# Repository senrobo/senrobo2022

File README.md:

# Sentinels Robotics

Yay we passed the 100th commit milestone
400 Commit milestone

## Checklist

### Mechanical

- Kicker Done on 20/1/2022

### Parts used

| Part Name    | Part Description                                               |
| ------------ | -------------------------------------------------------------- |
| OpenMV H7/R7 | Camera                                                         |
| MUX          | Multiplexer (https://www.ti.com/lit/ds/symlink/cd74hc4067.pdf) |

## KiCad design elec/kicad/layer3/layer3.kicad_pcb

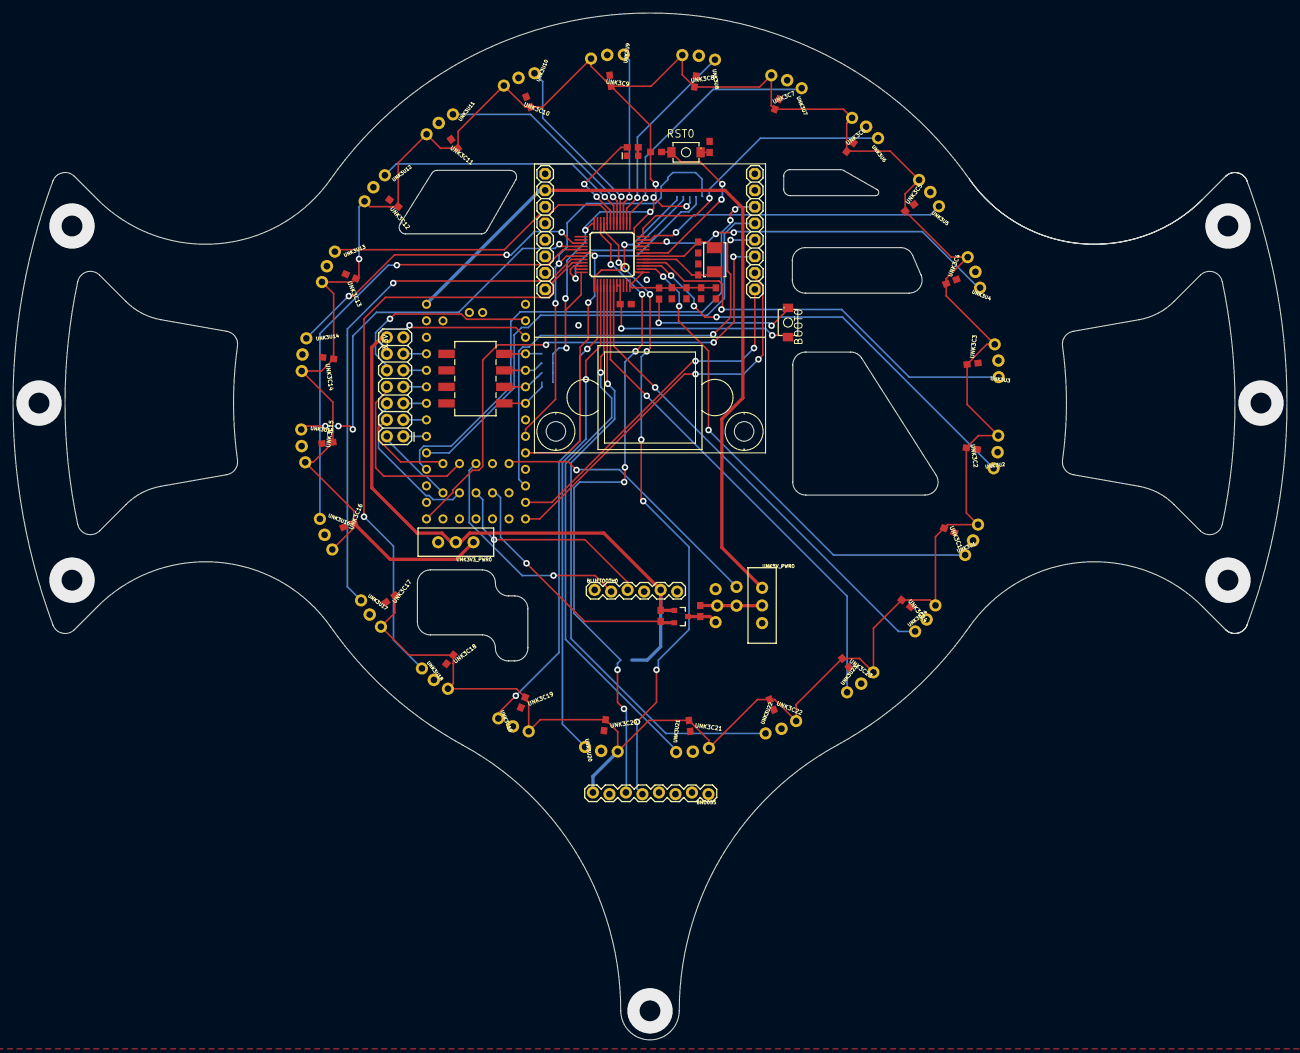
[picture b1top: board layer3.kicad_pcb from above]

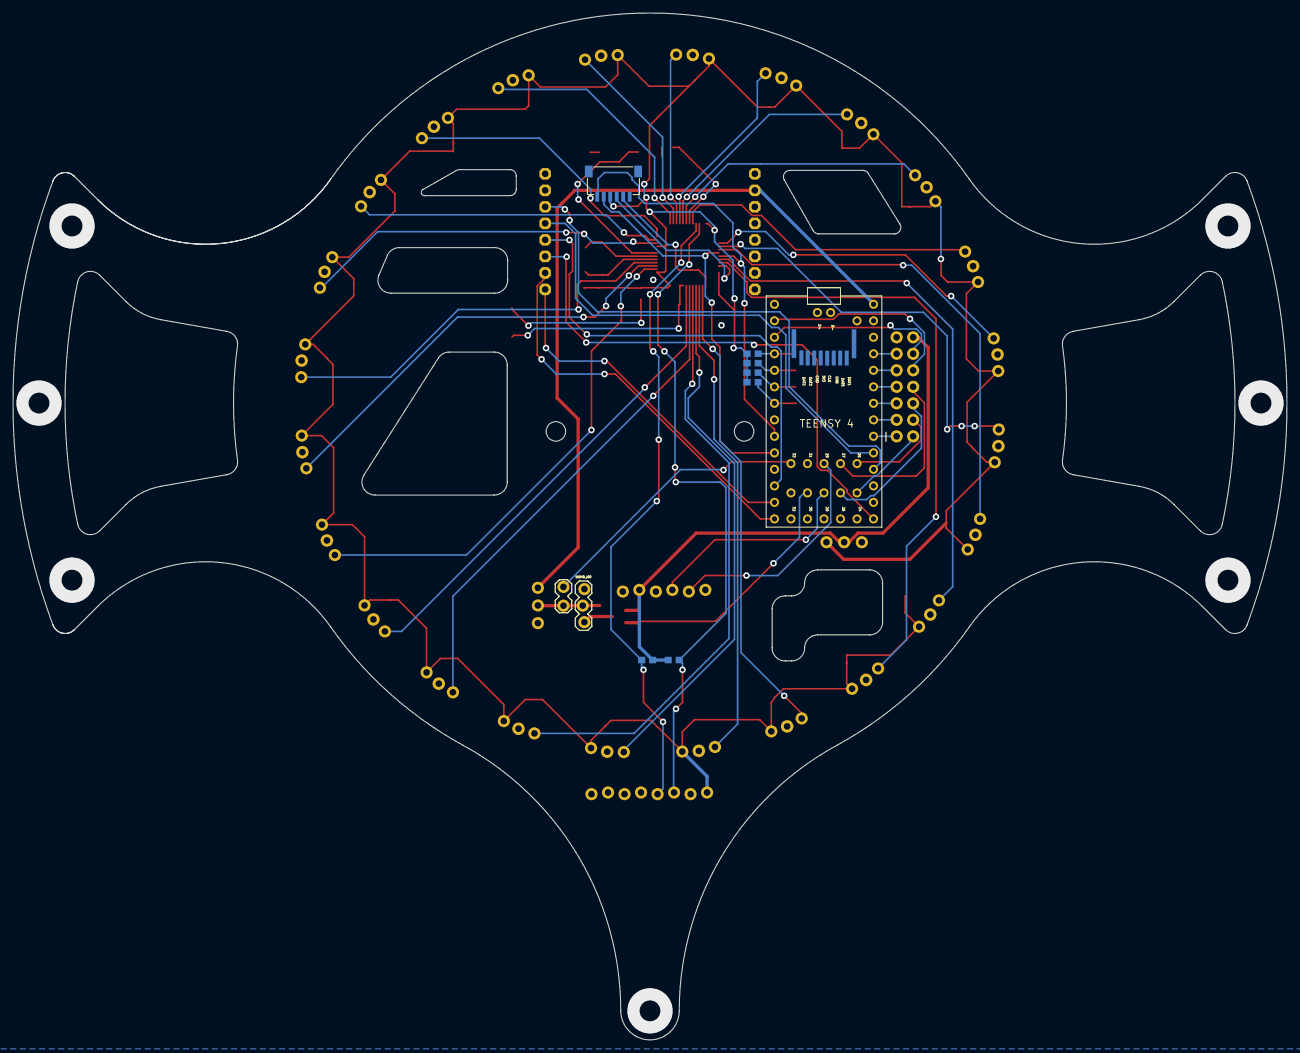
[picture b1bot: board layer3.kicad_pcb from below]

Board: 2 copper layers, 196.0 x 158.0 mm, 84 parts (10 on the bottom side), 70 nets.

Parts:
BLUETOOTH0: HC-05
BNO055: 1X08_LOCK
BOOT0: MOMENTARY_SWITCH_4X3
C1, C2, C3, C5: 1uF; C0603
C6, C7: 22pF; C0603
D1: BLUE; LED-0603
J1: 1X02_LOCK
Q2: AO3402; SOT23-3
R1, R4, R6, R7, R8, R9: 10k; R0603
R2, R3: 1k; R0603
R5: 470; R0603
R10, R11: 4.7k; 0603
R12, R13: 4.7k; R0603
RST0: MOMENTARY_SWITCH_4X3
S1: DIP-04SMD; DIPSWITCH-04-SMD
SERVO_IO0: 1X03_LOCK
STM32_IR0: STM32F103CBT6; LQFP48
TEENSY4: TEENSY-4.0-FULL-BREAKOUT-PINS
U$8: OPENMV3
U$14: CONN_07X2; 2X7
UNK3C1, UNK3C2, UNK3C3, UNK3C4, UNK3C5, UNK3C6, UNK3C7, UNK3C8, UNK3C9, UNK3C10, UNK3C11, UNK3C12, UNK3C13, UNK3C14, UNK3C15, UNK3C16, UNK3C17, UNK3C18, UNK3C19, UNK3C20, UNK3C21, UNK3C22, UNK3C23, UNK3C24: C0603
UNK3U1, UNK3U2, UNK3U3, UNK3U4, UNK3U5, UNK3U6, UNK3U7, UNK3U8, UNK3U9, UNK3U10, UNK3U11, UNK3U12, UNK3U13, UNK3U14, UNK3U15, UNK3U16, UNK3U17, UNK3U18, UNK3U19, UNK3U20, UNK3U21, UNK3U22, UNK3U23, UNK3U24: TSSP58038
UNK3V3_PWR0, UNK5V_PWR0: SWITCH_SPDT_PTH_11.6X4.0MM_LOCK
X1: SM06B-SRSS-TB
Y1: 8MHz; CRYSTAL-SMD-5X3.2-2PAD

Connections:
3.3V: BLUETOOTH0.5, Q2.1, R10.2, R11.2, R13.1, U$14.14, UNK3V3_PWR0.2
3V3_SWITCH: BNO055.8, C1.1, C2.1, C3.1, C5.2, R1.2, R3.2, R6.2, R7.2, R8.2, R9.2, STM32_IR0.1, STM32_IR0.9, STM32_IR0.24, STM32_IR0.36, STM32_IR0.48, UNK3C1.1, UNK3C2.1, UNK3C3.1, UNK3C4.1, UNK3C5.1, UNK3C6.1, UNK3C7.1, UNK3C8.1, UNK3C9.1, UNK3C10.1, UNK3C11.1, UNK3C12.1, UNK3C13.1, UNK3C14.1, UNK3C15.1, UNK3C16.1, UNK3C17.1, UNK3C18.1, UNK3C19.1, UNK3C20.1, UNK3C21.1, UNK3C22.1, UNK3C23.1, UNK3C24.1, UNK3U1.VS, UNK3U2.VS, UNK3U3.VS, UNK3U4.VS, UNK3U5.VS, UNK3U6.VS, UNK3U7.VS, UNK3U8.VS, UNK3U9.VS, UNK3U10.VS, UNK3U11.VS, UNK3U12.VS, UNK3U13.VS, UNK3U14.VS, UNK3U15.VS, UNK3U16.VS, UNK3U17.VS, UNK3U18.VS, UNK3U19.VS, UNK3U20.VS, UNK3U21.VS, UNK3U22.VS, UNK3U23.VS, UNK3U24.VS, UNK3V3_PWR0.1, X1.4
5V: J1.2, R12.1, SERVO_IO0.2, UNK5V_PWR0.2
5V_SWITCH: TEENSY4.VIN, U$8.27, UNK5V_PWR0.1
BATT_LVL: TEENSY4.D23/A9, U$14.11
BL_DIR: TEENSY4.D26, U$14.6
BL_PWM: TEENSY4.D20/A6, U$14.5
BOOT0: BOOT0.P$2, R4.2, STM32_IR0.44, STM32_IR0.45
BR_DIR: TEENSY4.D27, U$14.8
BR_PWM: TEENSY4.D21/A7, U$14.7
DIP1: R6.1, S1.1, TEENSY4.D2
DIP2: R7.1, S1.2, TEENSY4.D3
DIP3: R8.1, S1.3, TEENSY4.D4
DIP4: R9.1, S1.4, TEENSY4.D5
ESC_LV: J1.1, TEENSY4.D33
FL_DIR: TEENSY4.D24, U$14.2
FL_PWM: TEENSY4.D18/A4, U$14.1
FR_DIR: TEENSY4.D25, U$14.4
FR_PWM: TEENSY4.D19/A5, U$14.3
GND: BLUETOOTH0.4, BNO055.7, C1.2, C2.2, C3.2, C5.1, C6.1, C7.1, D1.C, R2.1, R4.1, S1.5, S1.6, S1.7, S1.8, SERVO_IO0.1, STM32_IR0.8, STM32_IR0.23, STM32_IR0.35, STM32_IR0.47, TEENSY4.GND, TEENSY4.GND@1, TEENSY4.GND@2, TEENSY4.P$11, TEENSY4.P$12, U$8.28, U$14.13, UNK3C1.2, UNK3C2.2, UNK3C3.2, UNK3C4.2, UNK3C5.2, UNK3C6.2, UNK3C7.2, UNK3C8.2, UNK3C9.2, UNK3C10.2, UNK3C11.2, UNK3C12.2, UNK3C13.2, UNK3C14.2, UNK3C15.2, UNK3C16.2, UNK3C17.2, UNK3C18.2, UNK3C19.2, UNK3C20.2, UNK3C21.2, UNK3C22.2, UNK3C23.2, UNK3C24.2, UNK3U1.GND, UNK3U2.GND, UNK3U3.GND, UNK3U4.GND, UNK3U5.GND, UNK3U6.GND, UNK3U7.GND, UNK3U8.GND, UNK3U9.GND, UNK3U10.GND, UNK3U11.GND, UNK3U12.GND, UNK3U13.GND, UNK3U14.GND, UNK3U15.GND, UNK3U16.GND, UNK3U17.GND, UNK3U18.GND, UNK3U19.GND, UNK3U20.GND, UNK3U21.GND, UNK3U22.GND, UNK3U23.GND, UNK3U24.GND, X1.1
IR1: STM32_IR0.2, UNK3U1.OUT
IR2: STM32_IR0.3, UNK3U2.OUT
IR3: STM32_IR0.4, UNK3U3.OUT
IR4: STM32_IR0.10, UNK3U4.OUT
IR5: STM32_IR0.11, UNK3U5.OUT
IR6: STM32_IR0.12, UNK3U6.OUT
IR7: STM32_IR0.13, UNK3U7.OUT
IR8: STM32_IR0.14, UNK3U8.OUT
IR9: STM32_IR0.15, UNK3U9.OUT
IR10: STM32_IR0.16, UNK3U10.OUT
IR11: STM32_IR0.17, UNK3U11.OUT
IR12: STM32_IR0.18, UNK3U12.OUT
IR13: STM32_IR0.20, UNK3U13.OUT
IR14: STM32_IR0.27, UNK3U14.OUT
IR15: STM32_IR0.28, UNK3U15.OUT
IR16: STM32_IR0.29, UNK3U16.OUT
IR17: STM32_IR0.32, UNK3U17.OUT
IR18: STM32_IR0.33, UNK3U18.OUT
IR19: STM32_IR0.38, UNK3U19.OUT
IR20: STM32_IR0.39, UNK3U20.OUT
IR21: STM32_IR0.40, UNK3U21.OUT
IR22: STM32_IR0.41, UNK3U22.OUT
IR23: STM32_IR0.42, UNK3U23.OUT
IR24: STM32_IR0.43, UNK3U24.OUT
LIGHT_INT: TEENSY4.D22/A8, U$14.9
MISO: TEENSY4.D12, U$8.12
MOSI: TEENSY4.D11, U$8.11
unnamed: R2.2, RST0.P$1
unnamed: BOOT0.P$1, R3.1
unnamed: R5.2, STM32_IR0.19
unnamed: D1.A, R5.1
OSC_IN: C6.2, STM32_IR0.5, Y1.P$2
OSC_OUT: C7.2, STM32_IR0.6, Y1.P$1
RESET: R1.1, RST0.P$2, STM32_IR0.7
RX1_ST2: STM32_IR0.31, TEENSY4.D7, X1.6
RX3_ST1: TEENSY4.D0, U$14.10
RX_BT: BLUETOOTH0.2, TEENSY4.D29
SCK: TEENSY4.D13/LED, U$8.13
SCL0_TEE: TEENSY4.D17/A3, U$8.15
SCL1: BNO055.5, R11.1, STM32_IR0.21
SDA0_TEE: TEENSY4.D16/A2, U$8.16
SDA1: BNO055.6, R10.1, STM32_IR0.22
SERVO_HV: Q2.3, R12.2, SERVO_IO0.3
SERVO_LV: Q2.2, R13.2, TEENSY4.D30
SS: TEENSY4.D10, U$8.14
SWCLK: STM32_IR0.37, X1.2
SWDIO: STM32_IR0.34, X1.3
TX1_ST2: STM32_IR0.30, TEENSY4.D8, X1.5
TX3_ST1: TEENSY4.D1, U$14.12
TX_BT: BLUETOOTH0.3, TEENSY4.D28

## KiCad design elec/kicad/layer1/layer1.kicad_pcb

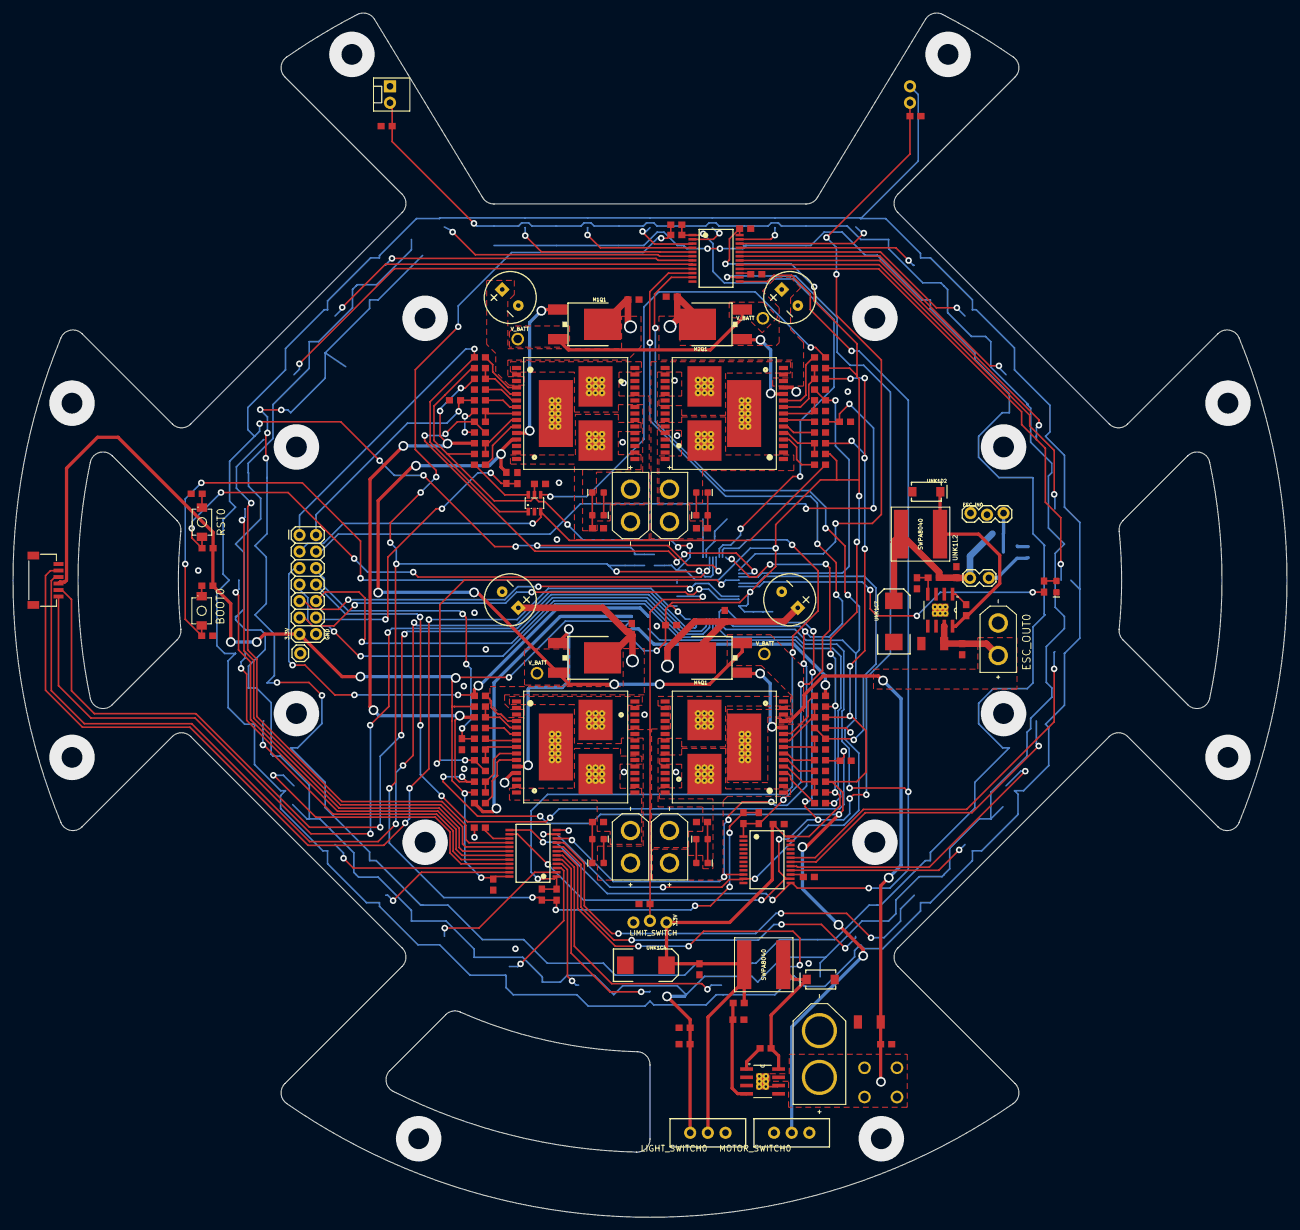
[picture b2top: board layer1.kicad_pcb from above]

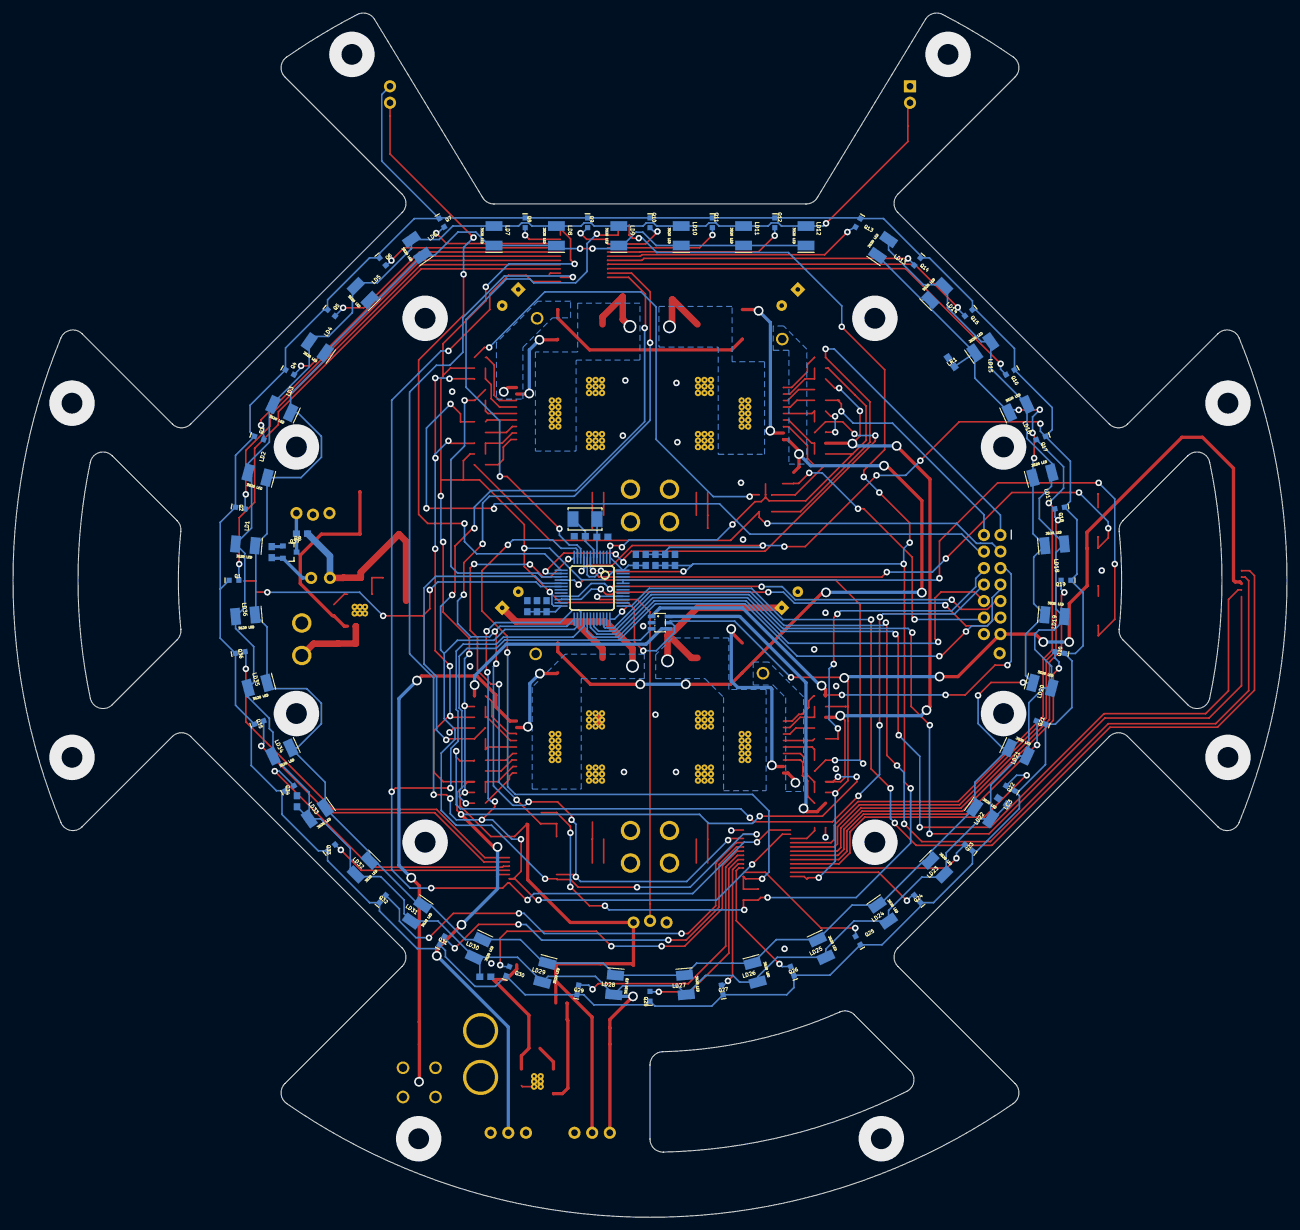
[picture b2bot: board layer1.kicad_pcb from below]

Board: 2 copper layers, 196.0 x 185.3 mm, 245 parts (92 on the bottom side), 146 nets.

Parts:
BOOT0: MOMENTARY_SWITCH_4X3
C1, C2, C3, C5, C8: 1uF; C0603
C4: 10nF; C0603
C6, C7: 22pF; C0603
D1: STM_LED; LED-0603
ESC_IN0: 1X03_LOCK
ESC_OUT0: XT30PB-F
FB1, FB2: 30Ω/1.8A; 0603
GND0: 1X01
J1: 1X02_LOCK
J2: 1X03_LOCK_NO_SILK
LC1, LC2, LC3, LC4, LC5, LC6: 1uF; C0603
LD1, LD2, LD3, LD4, LD5, LD6, LD7, LD8, LD9, LD10, LD11, LD12, LD13, LD14, LD15, LD16, LD17, LD18, LD19, LD20, LD21, LD22, LD23, LD24, LD25, LD26, LD27, LD28, LD29, LD30, LD31, LD32, LD33, LD34, LD35, LD36: 3528LED; 3528
LDR0: 1X02_NO_SILK
LED0: MOLEX-1X2
LG_R2: 2k; R0603
LIGHT_SWITCH0: SWITCH_SPDT_PTH_11.6X4.0MM_LOCK
LR1: 47; R0603
M1C1, M2C1, M3C1, M4C1: 33nF; C0603
M1C2, M2C2, M3C2, M4C2: 680uF; 3.5MM_CAP
M1C3, M2C3, M3C3, M4C3: 1.0uF; C0603
M1D1, M2D1, M3D1, M4D1: RED; LED-0603
M1D2, M2D2, M3D2, M4D2: BLUE; LED-0603
M1J1, M2J1, M3J1, M4J1: XT30PB-F
M1Q1, M2Q1, M3Q1, M4Q1: AOD482; DPAK
M1R1, M1R2, M1R5, M1R6, M1R7, M1R10, M2R1, M2R2, M2R5, M2R6, M2R7, M2R10, M3R1, M3R2, M3R5, M3R6, M3R7, M3R10, M4R1, M4R2, M4R5, M4R6, M4R7, M4R10: 1k; R0603
M1R3, M1R4, M2R3, M2R4, M3R3, M3R4, M4R3, M4R4: 3.3k; R0603
M1R8, M1R9, M1R11, M2R8, M2R9, M2R11, M3R8, M3R9, M3R11, M4R8, M4R9, M4R11: 10k; R0603
M1R12, M2R12, M3R12, M4R12: 4.7k; R0603
MOTOR_SWITCH0: SWITCH_SPDT_PTH_11.6X4.0MM_LOCK
MU1, MU2: SOT23-6
MUX_L1, MUX_L2, MUX_L3: SSOP24
M_BL0: VNH5019; POWERSO-30
M_BR0: VNH5019; POWERSO-30
M_FL0: VNH5019; POWERSO-30
M_FR0: VNH5019; POWERSO-30
Q1, Q2, Q3, Q4, Q5, Q6, Q7, Q8, Q9, Q10, Q11, Q12, Q13, Q14, Q15, Q16, Q17, Q18, Q19, Q20, Q21, Q22, Q23, Q24, Q25, Q26, Q27, Q28, Q29, Q30, Q31, Q32, Q33, Q34, Q35, Q36: ALS-PT19
Q37: AO3402; SOT23-3
R1, R4, R10: 10k; R0603
R2, R3: 1k; R0603
R5: 470; R0603
R6: 2M; R0603
R7: 500k; R0603
R8, R9: 4.7k; R0603
RST0: MOMENTARY_SWITCH_4X3
U1, U2: POWERPAD-SOIC-8
U$1: XT60XT60PB-M; XT60PB-M
U$2: STM32F103CBT6; LQFP48
U$15: CONN_07X2; 2X7
UNK1C1, UNK1C6: 4.7uF; C0603
UNK1C2, UNK1C10: 22uF; C1210
UNK1C3, UNK1C8: 10nF; C0603
UNK1C4, UNK1C7: 220uF; EIA7343
UNK1C5, UNK1C9, UNK2C1, UNK2C2, UNK2C3, UNK3C1, UNK3C2: 0.1uF; C0603
UNK1D1, UNK1D2: SS54; SMA-DIODE
UNK1L1, UNK1L2: 10uH; SWPA8040
UNK1R1, UNK1R3: 10k; R0603
UNK1R2: 5.9k; R0603
UNK1R4: 3.24k; R0603
UNK2C4, UNK2C5, UNK2C6: 1uF; C0603
UNK2R1, UNK2R2, UNK2R3: 1k; R0603
UNK2R4, UNK2R5, UNK2R6: 3k; R0603
V_BATT_M1A0, V_BATT_M1B0, V_BATT_M2A0, V_BATT_M2B0, V_BATT_M3A0, V_BATT_M3B0, V_BATT_M4A0, V_BATT_M4B0: 18AWG
X2: SM06B-SRSS-TB
Y1: 8MHz; CRYSTAL-SMD-5X3.2-2PAD

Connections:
3.3V: C1.1, C2.1, C3.1, C8.1, FB1.1, J2.1, LIGHT_SWITCH0.2, M1R3.2, M1R4.2, M2R3.2, M2R4.2, M3R3.2, M3R4.2, M4R3.2, M4R4.2, MU1.5, MU2.5, MUX_L1.24, MUX_L2.24, MUX_L3.24, R1.2, R3.2, U$2.1, U$2.24, U$2.36, U$2.48, U$15.13, UNK1C4.A, UNK1C5.1, UNK1L1.P2, UNK1R1.2, UNK2C1.1, UNK2C2.1, UNK2C3.1, UNK3C1.1, UNK3C2.1, X2.4
3.3V1: Q37.1, R9.1
5V: J1.2, R8.1, UNK1C7.A, UNK1C9.1, UNK1L2.P2, UNK1R3.2
AGND: C4.1, C5.1, FB2.2, U$2.8, UNK2C4.2, UNK2C5.2, UNK2C6.2, UNK2R4.1, UNK2R5.1, UNK2R6.1
BATT_LVL: R6.1, R7.2, U$15.12
BL_CS: M3C1.1, M3R8.1, U$2.16
BL_DIR: M3R5.1, MU2.1, U$15.5
BL_OUTA: M3D1.C, M3D2.A, M3J1.+, M_BL0.P1, M_BL0.P25, M_BL0.P30, M_BL0.P$1, M_BL0.P$2, M_BL0.P$3, M_BL0.P$4, M_BL0.P$5, M_BL0.P$6, M_BL0.P$7, M_BL0.P$8, M_BL0.P$9, M_BL0.SLUG2
BL_OUTB: M3J1.-, M3R12.2, M_BL0.P15, M_BL0.P16, M_BL0.P21, M_BL0.P$10, M_BL0.P$11, M_BL0.P$12, M_BL0.P$13, M_BL0.P$14, M_BL0.P$15, M_BL0.P$16, M_BL0.P$17, M_BL0.P$18, M_BL0.SLUG3
BL_PWM: M3R7.1, M3R11.2, U$15.6
BOOT0: BOOT0.P$2, R4.2, U$2.44, U$2.45
BR_CS: M4C1.1, M4R8.1, U$2.17
BR_DIR: M4R5.1, MU2.3, U$15.7
BR_OUTA: M4D1.C, M4D2.A, M4J1.+, M_BR0.P1, M_BR0.P25, M_BR0.P30, M_BR0.P$1, M_BR0.P$2, M_BR0.P$3, M_BR0.P$4, M_BR0.P$5, M_BR0.P$6, M_BR0.P$7, M_BR0.P$8, M_BR0.P$9, M_BR0.SLUG2
BR_OUTB: M4J1.-, M4R12.2, M_BR0.P15, M_BR0.P16, M_BR0.P21, M_BR0.P$10, M_BR0.P$11, M_BR0.P$12, M_BR0.P$13, M_BR0.P$14, M_BR0.P$15, M_BR0.P$16, M_BR0.P$17, M_BR0.P$18, M_BR0.SLUG3
BR_PWM: M4R7.1, M4R11.2, U$15.8
ESC_HV: ESC_IN0.3, Q37.3, R8.2
ESC_LV: J1.1, Q37.2, R9.2
FL_CS: M1C1.1, M1R8.1, U$2.14
FL_DIR: M1R5.1, MU1.1, U$15.1
FL_OUTA: M1D1.C, M1D2.A, M1J1.+, M_FL0.P1, M_FL0.P25, M_FL0.P30, M_FL0.P$1, M_FL0.P$2, M_FL0.P$3, M_FL0.P$4, M_FL0.P$5, M_FL0.P$6, M_FL0.P$7, M_FL0.P$8, M_FL0.P$9, M_FL0.SLUG2
FL_OUTB: M1J1.-, M1R12.2, M_FL0.P15, M_FL0.P16, M_FL0.P21, M_FL0.P$10, M_FL0.P$11, M_FL0.P$12, M_FL0.P$13, M_FL0.P$14, M_FL0.P$15, M_FL0.P$16, M_FL0.P$17, M_FL0.P$18, M_FL0.SLUG3
FL_PWM: M1R7.1, M1R11.2, U$15.2
FR_CS: M2C1.1, M2R8.1, U$2.15
FR_DIR: M2R5.1, MU1.3, U$15.3
FR_OUTA: M2D1.C, M2D2.A, M2J1.+, M_FR0.P1, M_FR0.P25, M_FR0.P30, M_FR0.P$1, M_FR0.P$2, M_FR0.P$3, M_FR0.P$4, M_FR0.P$5, M_FR0.P$6, M_FR0.P$7, M_FR0.P$8, M_FR0.P$9, M_FR0.SLUG2
FR_OUTB: M2J1.-, M2R12.2, M_FR0.P15, M_FR0.P16, M_FR0.P21, M_FR0.P$10, M_FR0.P$11, M_FR0.P$12, M_FR0.P$13, M_FR0.P$14, M_FR0.P$15, M_FR0.P$16, M_FR0.P$17, M_FR0.P$18, M_FR0.SLUG3
FR_PWM: M2R7.1, M2R11.2, U$15.4
GND: C1.2, C2.2, C3.2, C6.1, C7.1, C8.2, D1.C, ESC_IN0.1, ESC_OUT0.-, FB2.1, GND0.1, LC1.2, LC2.2, LC3.2, LC4.2, LC5.2, LC6.2, LED0.1, LG_R2.1, LR1.2, M1C1.2, M1C2.2, M1C3.2, M1R9.1, M1R10.1, M1R11.1, M2C1.2, M2C2.2, M2C3.2, M2R9.1, M2R10.1, M2R11.1, M3C1.2, M3C2.2, M3C3.2, M3R9.1, M3R10.1, M3R11.1, M4C1.2, M4C2.2, M4C3.2, M4R9.1, M4R10.1, M4R11.1, MOTOR_SWITCH0.1, MU1.2, MU2.2, MUX_L1.12, MUX_L2.12, MUX_L3.12, M_BL0.P18, M_BL0.P19, M_BL0.P20, M_BL0.P26, M_BL0.P27, M_BL0.P28, M_BR0.P18, M_BR0.P19, M_BR0.P20, M_BR0.P26, M_BR0.P27, M_BR0.P28, M_FL0.P18, M_FL0.P19, M_FL0.P20, M_FL0.P26, M_FL0.P27, M_FL0.P28, M_FR0.P18, M_FR0.P19, M_FR0.P20, M_FR0.P26, M_FR0.P27, M_FR0.P28, R2.1, R4.1, R7.1, R10.1, U1.6, U1.9, U1.P$1, U1.P$2, U1.P$3, U1.P$4, U1.P$5, U1.P$6, U2.6, U2.9, U2.P$1, U2.P$2, U2.P$3, U2.P$4, U2.P$5, U2.P$6, U$1.-, U$2.23, U$2.35, U$2.47, U$15.14, UNK1C1.2, UNK1C2.2, UNK1C4.C, UNK1C5.2, UNK1C6.2, UNK1C7.C, UNK1C9.2, UNK1C10.2, UNK1D1.A, UNK1D2.A, UNK1R2.1, UNK1R4.1, UNK2C1.2, UNK2C2.2, UNK2C3.2, UNK2R1.1, UNK2R2.1, UNK2R3.1, UNK3C1.2, UNK3C2.2, X2.1
LG_SIG: LDR0.2, LG_R2.2, U$2.13
LIGHT_INT: U$2.29, U$15.10
LIMIT_SWITCH: J2.2, R10.2, U$2.40
LS0: MUX_L1.10, MUX_L2.10, MUX_L3.10, U$2.25
LS1: MUX_L1.11, MUX_L2.11, MUX_L3.11, U$2.26
LS2: MUX_L1.14, MUX_L2.14, MUX_L3.14, U$2.27
LS3: MUX_L1.13, MUX_L2.13, MUX_L3.13, U$2.28
LSIG1: MUX_L1.1, U$2.10, UNK2C4.1, UNK2R4.2
LSIG2: MUX_L2.1, U$2.11, UNK2C5.1, UNK2R5.2
LSIG3: MUX_L3.1, U$2.12, UNK2C6.1, UNK2R6.2
LSWITCH: LC1.1, LC2.1, LC3.1, LC4.1, LC5.1, LC6.1, LD1.A, LD2.A, LD3.A, LD4.A, LD5.A, LD6.A, LD7.A, LD8.A, LD9.A, LD10.A, LD11.A, LD12.A, LD13.A, LD14.A, LD15.A, LD16.A, LD17.A, LD18.A, LD19.A, LD20.A, LD21.A, LD22.A, LD23.A, LD24.A, LD25.A, LD26.A, LD27.A, LD28.A, LD29.A, LD30.A, LD31.A, LD32.A, LD33.A, LD34.A, LD35.A, LD36.A, LED0.2, LIGHT_SWITCH0.1
M_SWITCH: M1R1.1, M1R2.1, M2R1.1, M2R2.1, M3R1.1, M3R2.1, M4R1.1, M4R2.1, MOTOR_SWITCH0.2
unnamed: U1.1, UNK1C3.1
unnamed: U1.8, UNK1C3.2, UNK1D1.C, UNK1L1.P1
unnamed: U2.8, UNK1C8.2, UNK1D2.C, UNK1L2.P1
unnamed: U1.4, UNK1R1.1, UNK1R2.2
unnamed: U2.4, UNK1R3.1, UNK1R4.2
unnamed: U2.1, UNK1C8.1
unnamed: M1R1.2, M1R4.1, M_FL0.P5
unnamed: M1R2.2, M1R3.1, M_FL0.P9
unnamed: M1R5.2, M_FL0.P4
unnamed: M1R6.2, M_FL0.P10
unnamed: M1R7.2, M_FL0.P7
unnamed: M1R8.2, M1R10.2, M_FL0.P8
unnamed: M1R9.2, M_FL0.P6
unnamed: M1C2.1, M1C3.1, M1Q1.4, M_FL0.P3, M_FL0.P13, M_FL0.P23, M_FL0.P$19, M_FL0.P$20, M_FL0.P$21, M_FL0.P$22, M_FL0.P$23, M_FL0.P$24, M_FL0.P$25, M_FL0.P$26, M_FL0.P$27, M_FL0.P$28, M_FL0.SLUG1
unnamed: M1Q1.1, M_FL0.P11
unnamed: M2R2.2, M2R3.1, M_FR0.P9
unnamed: M1D1.A, M1D2.C, M1R12.1
unnamed: M2R1.2, M2R4.1, M_FR0.P5
unnamed: M2R6.2, M_FR0.P10
unnamed: M2R5.2, M_FR0.P4
unnamed: M2R7.2, M_FR0.P7
unnamed: M2R8.2, M2R10.2, M_FR0.P8
unnamed: M2R9.2, M_FR0.P6
unnamed: M2C2.1, M2C3.1, M2Q1.4, M_FR0.P3, M_FR0.P13, M_FR0.P23, M_FR0.P$19, M_FR0.P$20, M_FR0.P$21, M_FR0.P$22, M_FR0.P$23, M_FR0.P$24, M_FR0.P$25, M_FR0.P$26, M_FR0.P$27, M_FR0.P$28, M_FR0.SLUG1
unnamed: M2Q1.1, M_FR0.P11
unnamed: M3R2.2, M3R3.1, M_BL0.P9
unnamed: M2D1.A, M2D2.C, M2R12.1
unnamed: M3R1.2, M3R4.1, M_BL0.P5
unnamed: M3R6.2, M_BL0.P10
unnamed: M3R5.2, M_BL0.P4
unnamed: M3R7.2, M_BL0.P7
unnamed: M3R8.2, M3R10.2, M_BL0.P8
unnamed: M3R9.2, M_BL0.P6
unnamed: M3C2.1, M3C3.1, M3Q1.4, M_BL0.P3, M_BL0.P13, M_BL0.P23, M_BL0.P$19, M_BL0.P$20, M_BL0.P$21, M_BL0.P$22, M_BL0.P$23, M_BL0.P$24, M_BL0.P$25, M_BL0.P$26, M_BL0.P$27, M_BL0.P$28, M_BL0.SLUG1
unnamed: M3Q1.1, M_BL0.P11
unnamed: M4R2.2, M4R3.1, M_BR0.P9
unnamed: M4R1.2, M4R4.1, M_BR0.P5
unnamed: M4R6.2, M_BR0.P10
unnamed: M4R5.2, M_BR0.P4
unnamed: M4R7.2, M_BR0.P7
unnamed: M3D1.A, M3D2.C, M3R12.1
unnamed: M4R8.2, M4R10.2, M_BR0.P8
unnamed: M4R9.2, M_BR0.P6
unnamed: M4C2.1, M4C3.1, M4Q1.4, M_BR0.P3, M_BR0.P13, M_BR0.P23, M_BR0.P$19, M_BR0.P$20, M_BR0.P$21, M_BR0.P$22, M_BR0.P$23, M_BR0.P$24, M_BR0.P$25, M_BR0.P$26, M_BR0.P$27, M_BR0.P$28, M_BR0.SLUG1
unnamed: M4Q1.1, M_BR0.P11
unnamed: M4D1.A, M4D2.C, M4R12.1
unnamed: MUX_L1.15, UNK2R1.2
unnamed: MUX_L1.16, Q1.E
unnamed: MUX_L1.17, Q2.E
unnamed: MUX_L1.18, Q3.E
unnamed: MUX_L1.19, Q4.E
unnamed: MUX_L1.20, Q5.E
unnamed: MUX_L1.21, Q6.E
unnamed: MUX_L1.22, Q7.E
unnamed: MUX_L1.23, Q8.E
unnamed: MUX_L1.2, Q9.E
unnamed: MUX_L1.3, Q10.E
unnamed: MUX_L1.4, Q11.E
unnamed: MUX_L1.5, Q12.E
unnamed: MUX_L1.6, Q13.E
unnamed: MUX_L1.7, Q14.E
unnamed: MUX_L1.8, Q15.E
unnamed: MUX_L1.9, Q16.E
unnamed: LD1.C, LD2.C, LD3.C, LD4.C, LD5.C, LD6.C, LD7.C, LD8.C, LD9.C, LD10.C, LD11.C, LD12.C, LD13.C, LD14.C, LD15.C, LD16.C, LD17.C, LD18.C, LD19.C, LD20.C, LD21.C, LD22.C, LD23.C, LD24.C, LD25.C, LD26.C, LD27.C, LD28.C, LD29.C, LD30.C, LD31.C, LD32.C, LD33.C, LD34.C, LD35.C, LD36.C, LR1.1
unnamed: R2.2, RST0.P$1
unnamed: BOOT0.P$1, R3.1
unnamed: R5.2, U$2.18
unnamed: D1.A, R5.1
unnamed: MUX_L2.15, UNK2R2.2
unnamed: MUX_L2.16, Q17.E
unnamed: MUX_L2.17, Q18.E
unnamed: MUX_L2.18, Q19.E
unnamed: MUX_L2.19, Q20.E
unnamed: MUX_L2.20, Q21.E
unnamed: MUX_L2.21, Q22.E
unnamed: MUX_L2.22, Q23.E
unnamed: MUX_L2.23, Q24.E
unnamed: MUX_L2.2, Q25.E
unnamed: MUX_L2.3, Q26.E
unnamed: MUX_L2.4, Q27.E
unnamed: MUX_L2.5, Q28.E
unnamed: MUX_L2.6, Q29.E
unnamed: MUX_L2.7, Q30.E
unnamed: MUX_L2.8, Q31.E
unnamed: MUX_L2.9, Q32.E
unnamed: MUX_L3.15, UNK2R3.2
unnamed: MUX_L3.16, Q33.E
unnamed: MUX_L3.17, Q34.E
unnamed: MUX_L3.18, Q35.E
unnamed: MUX_L3.19, Q36.E
NOT_BL_DIR: M3R6.1, MU2.6
NOT_BR_DIR: M4R6.1, MU2.4
NOT_FL_DIR: M1R6.1, MU1.6
NOT_FR_DIR: M2R6.1, MU1.4
OSC_IN: C6.2, U$2.5, Y1.P$2
OSC_OUT: C7.2, U$2.6, Y1.P$1
RESET: R1.1, RST0.P$2, U$2.7
RX1: U$2.31, X2.6
RX3: U$2.22, U$15.11
SWCLK: U$2.37, X2.2
SWDIO: U$2.34, X2.3
TX1: U$2.30, X2.5
TX3: U$2.21, U$15.9
VCCA: C4.2, C5.2, FB1.2, LDR0.1, Q1.C, Q2.C, Q3.C, Q4.C, Q5.C, Q6.C, Q7.C, Q8.C, Q9.C, Q10.C, Q11.C, Q12.C, Q13.C, Q14.C, Q15.C, Q16.C, Q17.C, Q18.C, Q19.C, Q20.C, Q21.C, Q22.C, Q23.C, Q24.C, Q25.C, Q26.C, Q27.C, Q28.C, Q29.C, Q30.C, Q31.C, Q32.C, Q33.C, Q34.C, Q35.C, Q36.C, U$2.9
V_BATT: ESC_OUT0.+, M1Q1.3, M2Q1.3, M3Q1.3, M4Q1.3, M_BL0.P12, M_BR0.P12, M_FL0.P12, M_FR0.P12, R6.2, U1.7, U2.7, U$1.+, UNK1C1.1, UNK1C2.1, UNK1C6.1, UNK1C10.1, V_BATT_M1A0.P$1, V_BATT_M1B0.P$1, V_BATT_M2A0.P$1, V_BATT_M2B0.P$1, V_BATT_M3A0.P$1, V_BATT_M3B0.P$1, V_BATT_M4A0.P$1, V_BATT_M4B0.P$1

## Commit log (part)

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2021-11-25 added layer1 and layer2 pdf
2021-11-25 moved v1 folder to .pdf folder
2021-11-25 added gcode and stl
2021-11-25 updated dribbler mount & plate, added dribbler spaces
2021-11-26 updated motor mount and added missing holes for motor to layer 2
2021-11-26 cool
2021-11-26 file
2021-11-26 eagle layer 3
2021-11-26 added layer 3
2021-11-26 updated eagle file
2021-11-26 Eagle
2021-11-27 Added excel
2021-11-27 Added Sketches
2021-11-27 layer 3
2021-11-27 Added stands
2021-11-27 I am done i think
2021-11-27 Added alu stands as alternative
2021-11-27 included sketches layer 3 n 4
2021-11-28 added dxf files for layer 3 and 4
2021-11-29 added docs folder
2021-11-29 added cam and dru folder
2021-11-29 final file
2021-11-29 autocad
2021-11-29 cancer pain in the ass
2021-11-30 edit
2021-12-01 layer 4 sch
2021-12-01 added assets: limitswitch.dwg
2021-12-01 layer 2
2021-12-01 added layer 4 file
2021-12-01 layer 3 update
2021-12-01 updated limitswitch.dwg
2021-12-01 more shit need to do
2021-12-01 about done
2021-12-01 done with layer 4
2021-12-01 changes to layout in layer 3
2021-12-01 change sch
2021-12-01 editied layers
2021-12-01 forgot to save
2021-12-02 added 2mm spacers
2021-12-02 switch hole
2021-12-02 modified layers 3 and 4
2021-12-02 knn smlj
2021-12-03 added blackflipswitch.stl
2021-12-03 added blackflipswitch.dwg asset
2021-12-03 changed layer 2 to 3 mount height
2021-12-03 handle sketches
2021-12-03 Layer 4 Sketches
2021-12-03 Added DXF
2021-12-03 added layers dxf
2021-12-03 balls
2021-12-03 lol ono
2021-12-06 added m3nut.dwg
2021-12-06 did sanity check on bot
2021-12-06 removed .pdf files
2021-12-06 removed .dxf sketches
2021-12-06 updated layer 3 dxf
2021-12-06 done with layer 3 schem
2021-12-08 fat fuck balls
2021-12-08 fuck you yun song
2021-12-08 suck my balls
2022-01-04 left with calculations
2022-01-04 homer monkey brain
2022-01-04 commit literally nothing
2022-01-11 modelled new kicker and updated layer1.dxf
2022-01-11 redoing the kicker
2022-01-12 modelled new kicker and created kicker parts stl files
2022-01-12 added cura profs
2022-01-13 removed fillet in the kicker
2022-01-13 redesigned kicker to second later
2022-01-14 kicker parts gcode
2022-01-14 kicker update
2022-01-14 added layer1v2
2022-01-14 re uploaded layer1v2.dxf
2022-01-14 added old folder in .dxf
2022-01-14 added old folder to .pdf
2022-01-14 added .pdf for each layers
2022-01-14 exported .pdf files to .ai
2022-01-15 added .iges and removed switch hole from layer 2
2022-01-15 Updated Layer 3 with new DXF
2022-01-15 Added word to handle
2022-01-17 Added layer 3pcb
2022-01-17 🚀🚀🚀 Edited Layer 3 and 4 Changed the positioning of the BT Module Change the positioning of the connectors
2022-01-17 😭fusion and autocad bully me
2022-01-18 🥰 Layer 3 Edits Changed oreintation of XH Connectors Shrunk the radius of IR Sensor
2022-01-18 🚒🔥Tired Added IR Guard
2022-01-18 💀 Edited IR Guard
2022-01-18 🛌 Imma head to bed
2022-01-19 💰 part list
2022-01-19 the fuck
2022-01-19 help
2022-01-19 clean
2022-01-19 somehow zeus doesnt upload eagle
2022-01-19 💀 Almost died again thank god hv backup
2022-01-19 fucked up
2022-01-19 🏭 Added CAM File 🏭
2022-01-19 added .zip folder
2022-01-19 added folder for icon
2022-01-20 😎 Added stuff done in readme
2022-01-20 tried gear in autocad but failed
2022-01-20 updated kicker to v4, corrected slanted faces on kicker
2022-01-20 updated kicker to v4, corrected slanted faces on kicker (recommit)
2022-01-20 added old directory in eagle/assets
2022-01-20 🥳🎇🎆🎉 Done with the mirror
2022-01-20 cut holes in layer 4 and added dxf layer 4 v2
2022-01-20 cut holes in layer 4 and added dxf layer 4 v2 (recommit)
2022-01-20 updated .gitignore in .dwg/final
2022-01-20 changed colours for layers in Final dwg
2022-01-20 edited kicker
2022-01-20 yeet
2022-01-20 penis
2022-01-20 🦅 Included Layer 4 new
2022-01-20 🦅 Edited Layer 3 Testing Git LFS
2022-01-20 edited Git LFS
2022-01-20 😩 fml
2022-01-21 renamed final files
2022-01-21 created layer4v3.dxf
2022-01-21 step
2022-01-21 add layer 4 .pdf and .ai
2022-01-21 added mg90s servo dwg model
2022-01-21 🏎 git push️
2022-01-21 halfway done with servo mount
2022-01-21 Made the servo mount Havent added holes
2022-01-21 🦅 Layer 3 AGAIN
2022-01-21 fuck me
2022-01-21 removed mouse sensor
2022-01-21 oh no
2022-01-21 depression
2022-01-22 depressionv2
2022-01-22 depressionv3
2022-01-22 depressionv4
2022-01-22 depressionv5
2022-01-22 depressionv6
2022-01-22 depressionv7
2022-01-22 edited layer 1
2022-01-24 cut holes in layer 2 and 3 for servo mount and update dxf (not plotted and no ai files yet)
2022-01-26 cut mirrored hole in layer 2
2022-01-26 recommit
2022-01-27 168 airwires left
2022-01-27 130 airwires left
2022-01-27 121 airwires left mostly stm32
2022-01-27 routed some to STEM32
2022-01-27 Added A shit ton of polygons arnd the motor
2022-01-27 Added a shit ton of polygons
2022-01-28 Brainfuck
2022-01-28 62 airwires
2022-01-28 63 airwires
2022-01-28 29 airwires left
2022-01-28 27 airwires left
2022-01-28 18 airwires left
2022-01-28 10 airwires left
2022-01-28 5 airwires left
2022-01-28 Done with layer 1
2022-01-28 fuck
2022-01-28 fuck eagle dying again
2022-01-29 braindead
2022-01-29 fixed
2022-02-05 edited layer 1 holes to vias
2022-02-05 redid layer 1
2022-02-05 redid layer 1 paining
2022-02-05 removed some words
2022-02-05 edited via size
2022-02-06 edited layer 3 bt module
2022-02-06 edited layer 3 vias
2022-02-07 retarded 🦅
2022-02-08 layer 2 dxf not completed
2022-02-09 updated layer 5 dxf (v5)
2022-02-09 taobao
2022-02-09 layer2v6
2022-02-09 exported new stl files
2022-02-09 sliced gcode file for kicker and servo parts
2022-02-09 incomplete
2022-02-09 all parts here but quite messy
2022-02-10 retarded taobao
2022-02-11 drew new layer 2 dxf (v7)
2022-02-11 dgfhrg
2022-02-11 updated all layers dxf
2022-02-11 updated all layers dxf recommit
2022-02-11 moved layer 1
2022-02-11 moved layer 1 again
2022-02-11 layer1v8
2022-02-11 incomplete layer 1
2022-02-11 completed layer1, vincent check now
2022-02-11 aligned layers 3 and 4 to geom center in dxf files
2022-02-13 retarded 🦅 just moved one line
2022-02-18 layers 1, 3, 4 complete, layer 2 need to change holes to green color thingy?
2022-02-18 stuff added to layer2
2022-02-21 retarded 🦅 Layer 1 Finished Checking
2022-02-21 deleted useless fiels
2022-02-21 Added limit switch
2022-02-21 layer 1 v10 dxf
2022-02-21 layer2 v9 dxf
2022-02-21 Edited PCB for larger catchment area
2022-02-21 fixed issues on layer 1
2022-02-21 Modified more stuff
2022-02-21 Fixed a wire stub
2022-02-21 Fixed more stuff
2022-02-22 layer2 v10 dxf
2022-02-22 Retarded eagle
2022-02-22 Final Check
2022-02-22 Added GND Connector
2022-02-22 More taobao
2022-02-23 Edited Layer 4
2022-02-23 primt file
2022-02-23 Edited PCB
2022-02-23 Final PCB
2022-02-23 Vincent please dont touch pcb anymore focus on studies
2022-02-23 Made all the standoff vias GND
2022-02-23 Undid changes
2022-02-23 Removed Motor Ground and Added battery mount holes
2022-02-23 fucking done pls vincent dont touch it AGAIN
2022-02-24 Removed Layer 4 and moved all layer 4 to 3
2022-02-24 Redoing the positioning of the motor driver power supply and changed the battery mount holes
2022-02-24 Did FL and FR Motors
2022-02-24 Did BL Motor
2022-02-24 Finished
2022-02-25 Depressed 🦅
2022-02-25 Depressed 🦅 Layer 1
2022-02-25 moved v10layer to old folder
2022-02-25 All layers have frames
2022-02-25 layer4v4 dxf
2022-02-25 Done layer 1
2022-02-25 gerber
2022-02-26 layer 2 update v12
2022-02-26 fuck i do eagle again
2022-02-26 final
2022-02-28 Changing 3.6 to 4.0
2022-02-28 final integration of teensy 4 to board
2022-02-28 added teensy 4 lbr
2022-02-28 cut more holes beech
2022-03-01 Edited teensy 4 pin out
2022-03-01 Added Cura settings
2022-03-01 Sent to SRC
2022-03-02 logo
2022-03-02 Arduino
2022-03-02 fuck man i paid 4 bucks for this
2022-03-02 graphics
2022-03-03 Programming
2022-03-04 servo mount
2022-03-04 profile
2022-03-04 things
2022-03-04 Edited cura
2022-03-04 servo mount done
2022-03-04 lmao servo mount?
2022-03-04 gcode
2022-03-06 servo mount design new
2022-03-06 new layer 1.5
2022-03-06 mesh design cutouts in layer1.5
2022-03-08 new slope design
2022-03-08 mirrorLayer4 stl
2022-03-09 layer2 pdf
2022-03-09 layer2 ai file
2022-03-11 light sensor
2022-03-11 edited stuff
2022-03-11 argh dirbbler ausdhauidhiawd
2022-03-14 updated rollers stl
2022-03-21 added new cura
2022-03-22 i didnt know i didnt commit
2022-03-25 new drbbler wall
2022-03-25 layer 2 update + stl files
2022-03-26 purge
2022-03-30 stuff
2022-03-30 kicad
2022-03-30 gcode print
2022-04-01 sen logo
2022-04-01 layer 2 update
2022-04-03 layer2 brd changed
2022-04-03 bmp logo
2022-04-08 layer 4v5 dxf
2022-04-08 fixed buggy graphics folder gi
2022-04-08 layer 4 pcb
2022-04-09 layer4
2022-04-09 remove kicad
2022-04-14 Create LICENSE
2022-04-14 stl updates
2022-04-16 updated dribbler mount with stl
2022-04-18 dk what
2022-04-21 rearranged stl files, exported gcode part 1
2022-04-22 -g push
2022-04-22 r plate stl dribbler
2022-04-22 new g code print
2022-05-21 layer 4 ultrasonic
2023-06-11 submissions
